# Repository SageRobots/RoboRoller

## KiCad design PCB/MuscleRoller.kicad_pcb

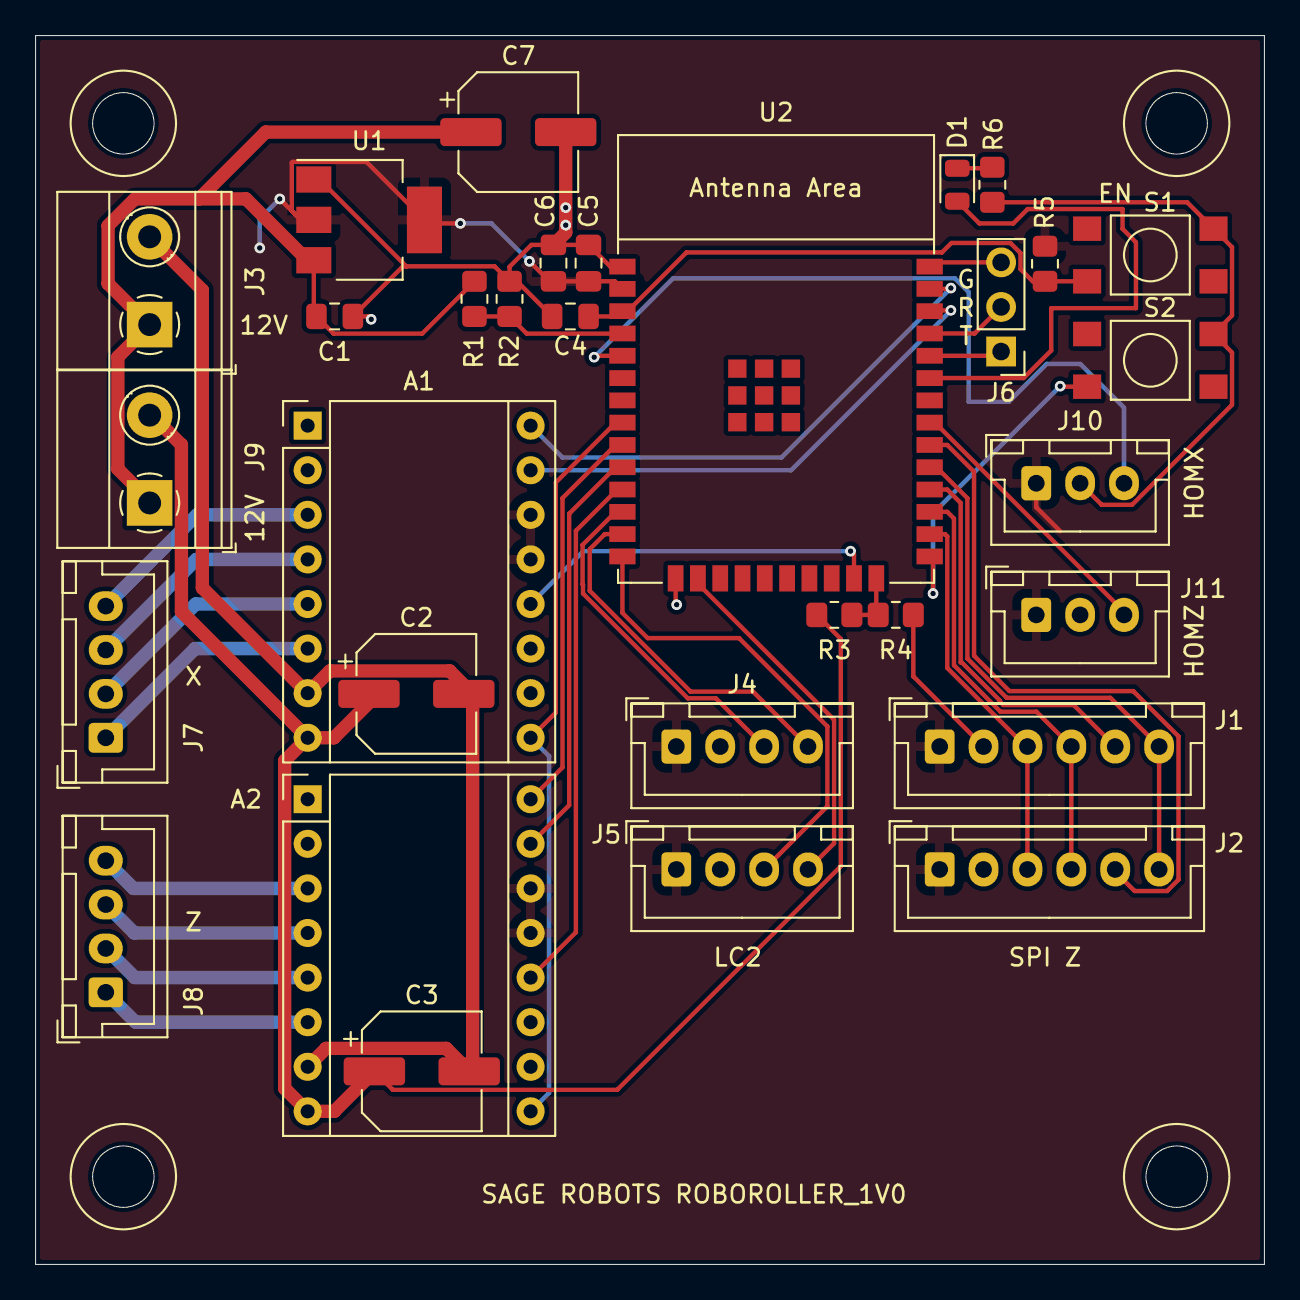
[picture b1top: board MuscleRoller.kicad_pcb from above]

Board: 2 copper layers, 70.0 x 70.0 mm, 31 parts (0 on the bottom side), 38 nets.

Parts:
A1, A2: Pololu_Breakout_DRV8825; Pololu_Breakout-16_15.2x20.3mm
C1: 22u; C_0805_2012Metric_Pad1.18x1.45mm_HandSolder
C2, C3, C7: 100u; CP_Elec_6.3x7.7
C4: 1u; C_0805_2012Metric_Pad1.18x1.45mm_HandSolder
C5: 22U; C_0805_2012Metric_Pad1.18x1.45mm_HandSolder
C6: 0.1u; C_0805_2012Metric_Pad1.18x1.45mm_HandSolder
D1: LED; LED_0805_2012Metric
J1, J2: Conn_01x06_Male; JST_XH_B6B-XH-A_1x06_P2.50mm_Vertical
J3, J9: Screw_Terminal_01x02; TerminalBlock_Phoenix_MKDS-1,5-2_1x02_P5.00mm_Horizontal
J4, J5, J7, J8: Conn_01x04_Male; JST_XH_B4B-XH-A_1x04_P2.50mm_Vertical
J6: Conn_01x03_Male; PinHeader_1x03_P2.54mm_Vertical
J10, J11: Conn_01x03_Male; JST_XH_B3B-XH-A_1x03_P2.50mm_Vertical
R1, R3: 47k; R_0805_2012Metric_Pad1.20x1.40mm_HandSolder
R2, R4, R5: 10K; R_0805_2012Metric_Pad1.20x1.40mm_HandSolder
R6: 100; R_0805_2012Metric_Pad1.20x1.40mm_HandSolder
S1, S2: TL3315NF160Q; TL3305AF160QG
U1: AZ1117-3.3; SOT-223-3_TabPin2
U2: ESP32-WROOM-E; ESP32-WROOM-32E

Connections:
+3V3: A1.13 (~RST), A1.14 (~SLP), A2.13 (~RST), A2.14 (~SLP), C5.1, C6.1, J1.1, J2.1, J4.1, J5.1, J10.1, J11.1, R5.1, U1.2 (VO), U2.2 (3V3)
+12V: C1.1, C7.1, J3.1, J9.1, R1.1, U1.3 (VI)
CHARGE: R1.2, R2.1, U2.4 (SENSOR_VP/GPIO36/ADC1_CH0)
CLK: J1.3, J2.3, U2.26 (ADC2_CH0/GPIO4)
CS0: J1.5, U2.28 (GPIO17)
CS1: J2.5, U2.30 (GPIO18)
DIRX: A1.16 (DIR), U2.37 (GPIO23)
DIRZ: A2.16 (DIR), U2.9 (32K_XN/GPIO33/ADC1_CH5)
EN: C4.1, R5.2, S1.1, U2.3 (EN/CHIP_PU)
EN_STEP: A1.9 (~EN), A2.9 (~EN), U2.8 (32K_XP/GPIO32/ADC1_CH4)
ESTOP: R3.2, R4.1, U2.24 (ADC2_CH2/GPIO2)
ESTOP12V: A1.8 (VMOT), A2.8 (VMOT), C2.1, C3.1, J9.2, R3.1
GND: A1.1 (GND), A1.7 (GND), A2.1 (GND), A2.7 (GND), C1.2, C2.2, C3.2, C4.2, C5.2, C6.2, C7.2, J1.2, J2.2, J3.2, J4.2, J5.2, J6.3, J10.2, J11.2, R2.2, R4.2, R6.2, S1.4, S2.4, U1.1 (GND), U2.1 (GND), U2.15 (GND), U2.38 (GND)
HOMX: J10.3, U2.5 (SENSOR_VN/GPIO39/ADC1_CH3)
HOMZ: J11.3, U2.31 (GPIO19)
IO0: S2.1, U2.25 (GPIO0/BOOT/ADC2_CH1)
LC_CLK: J4.3, U2.12 (ADC2_CH7/GPIO27)
LC_CLK2: J5.3, U2.14 (MTDI/GPIO12/ADC2_CH5)
LC_DAT: J4.4, U2.13 (MTMS/GPIO14/ADC2_CH6)
LC_DAT2: J5.4, U2.16 (MTCK/GPIO13/ADC2_CH4)
LED: D1.2 (A), U2.33 (GPIO21)
MISO: J1.4, J2.4, U2.27 (GPIO16)
MOSI: J1.6, J2.6, U2.29 (GPIO5)
MSX: A1.12 (M2), U2.23 (MTDO/GPIO15/ADC2_CH3)
MSZ: A2.12 (M2), U2.11 (DAC_2/ADC2_CH9/GPIO26)
unnamed: D1.1 (K), R6.1
RX: J6.2, U2.35 (U0TXD/GPIO1)
STEPX: A1.15 (STEP), U2.36 (GPIO22)
STEPZ: A2.15 (STEP), U2.10 (DAC_1/ADC2_CH8/GPIO25)
TX: J6.1, U2.34 (U0RXD/GPIO3)
XA1: A1.4 (A1), J7.3
XA2: A1.3 (A2), J7.4
XB1: A1.5 (B1), J7.2
XB2: A1.6 (B2), J7.1
ZA1: A2.4 (A1), J8.3
ZA2: A2.3 (A2), J8.4
ZB1: A2.5 (B1), J8.2
ZB2: A2.6 (B2), J8.1

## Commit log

2021-10-22 CARRIAGE-X
2021-10-22 spring loaded roller
2021-10-22 adding load cells
2021-10-22 finished x axis
2021-10-27 improved Z carriage
2021-10-28 lower frame
2021-10-28 x axis ready to build
2021-10-28 created animation
2021-10-28 base update
2021-10-29 base svg
2021-11-02 schematic
2021-11-03 PCB complete
2021-11-04 PCB order
2021-11-18 code for moves
2021-11-19 x position and speed code
2021-11-19 Motor gear ratio change
2021-11-22 x and z positioning
    x homing
2021-11-22 added load cell 1
2021-11-23 both load cells
    still need to move z in force mode in ISR
2021-11-24 load cell amp mounting
2021-11-24 x cable carrier
2021-11-26 fully functional
2021-12-02 Start of cantilever design
2021-12-02 Frame complete
2021-12-03 Added X motor
2021-12-04 Rail updates
    Added holes
2021-12-05 Added Z motor
2021-12-08 cycle code ip
2021-12-09 cycling functional
2021-12-09 started z guide rail
2021-12-10 Z rail design complete
2021-12-14 renaming parts
2021-12-15 carrier brackets
2021-12-16 base drawing
2021-12-27 Bigger brackets
2022-01-10 X rails and encoder
2022-01-11 CAD updates
2022-01-18 switch to ESP32 from ESP32-S2 for bluetooth
2022-01-22 gerber files
2022-01-26 BOM updates
2022-01-28 BOM and CAD updates
2022-06-04 BOM updates, design fixes
2022-07-13 code dev
2022-07-14 code updates
2022-07-14 debugging
2022-07-20 Debugging
    Need to try updating esp-idf version
2022-07-21 Compiles
2022-07-22 encoders working
2022-07-24 GPIO pin updates complete
2022-07-25 Magnet brackets for homing
2022-07-26 BOM resistor labels
2022-08-03 GPIO number updates
2022-08-03 hom x functional
2022-08-04 Need speed MS logic
2022-08-04 speed
2022-08-04 Speed and homing functional
2022-08-04 Cal code
2022-08-09 R1 R2 labels were positioned incorrectly
2022-08-10 Load cell cal
    Clock pin 2 needed manual configuration
2022-08-10 Ready to program cycle
2022-08-11 bluetooth ready to test serial command movex
2022-08-13 Started node bluetooth app for control
2022-08-22 fully functional bluetooth control
2022-08-24 Added LED for status, C7 for ESD protection
2022-08-25 BOM updates, x home sensor position update in CAD
